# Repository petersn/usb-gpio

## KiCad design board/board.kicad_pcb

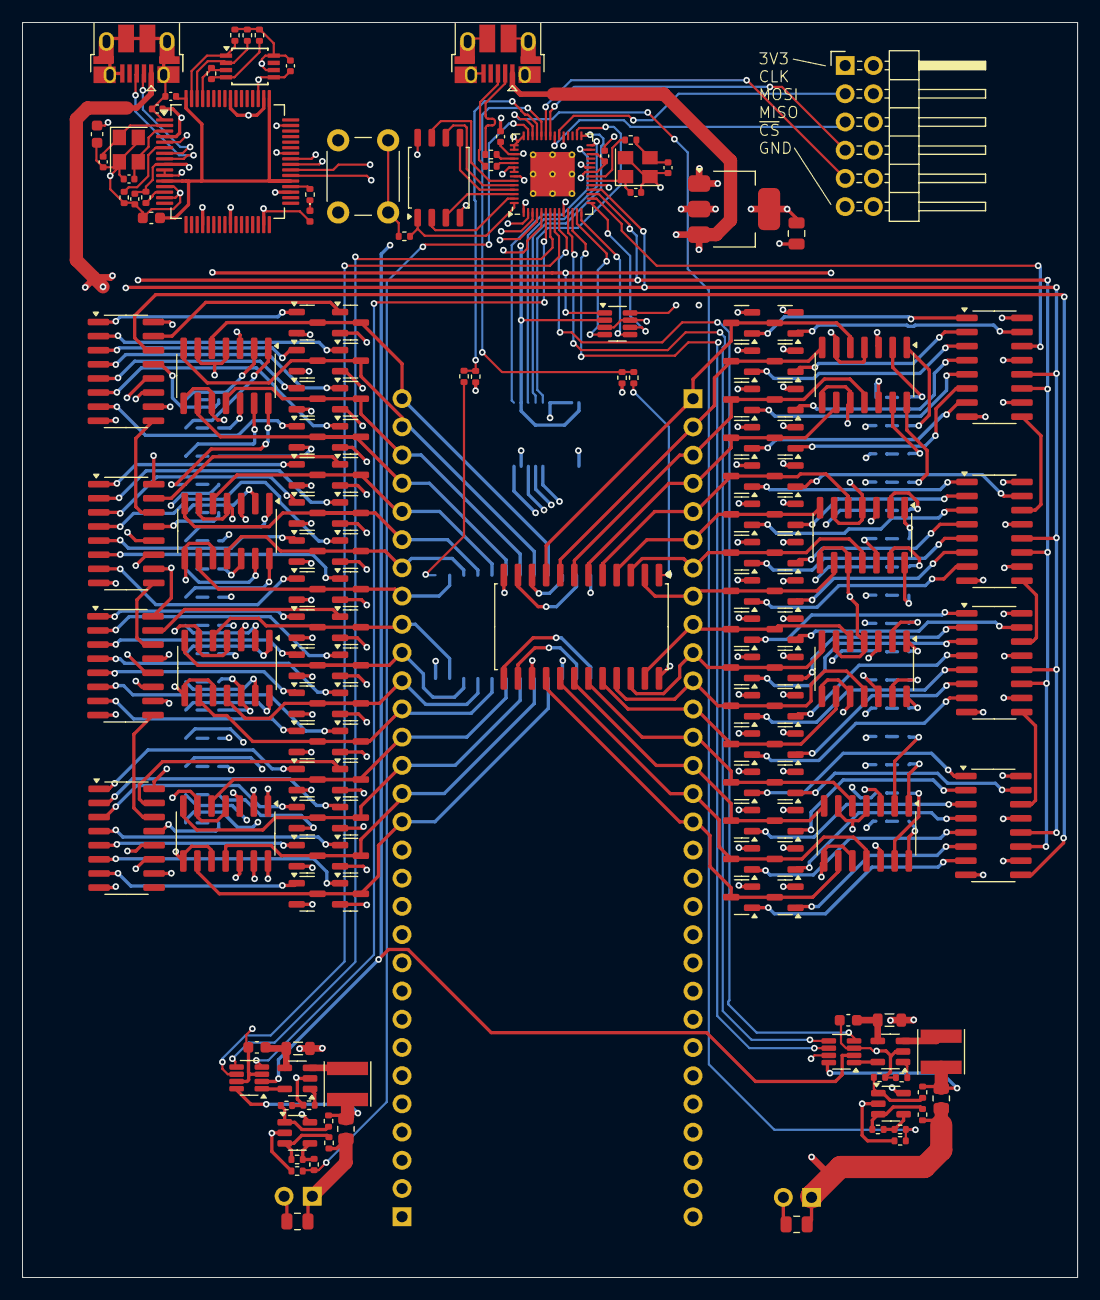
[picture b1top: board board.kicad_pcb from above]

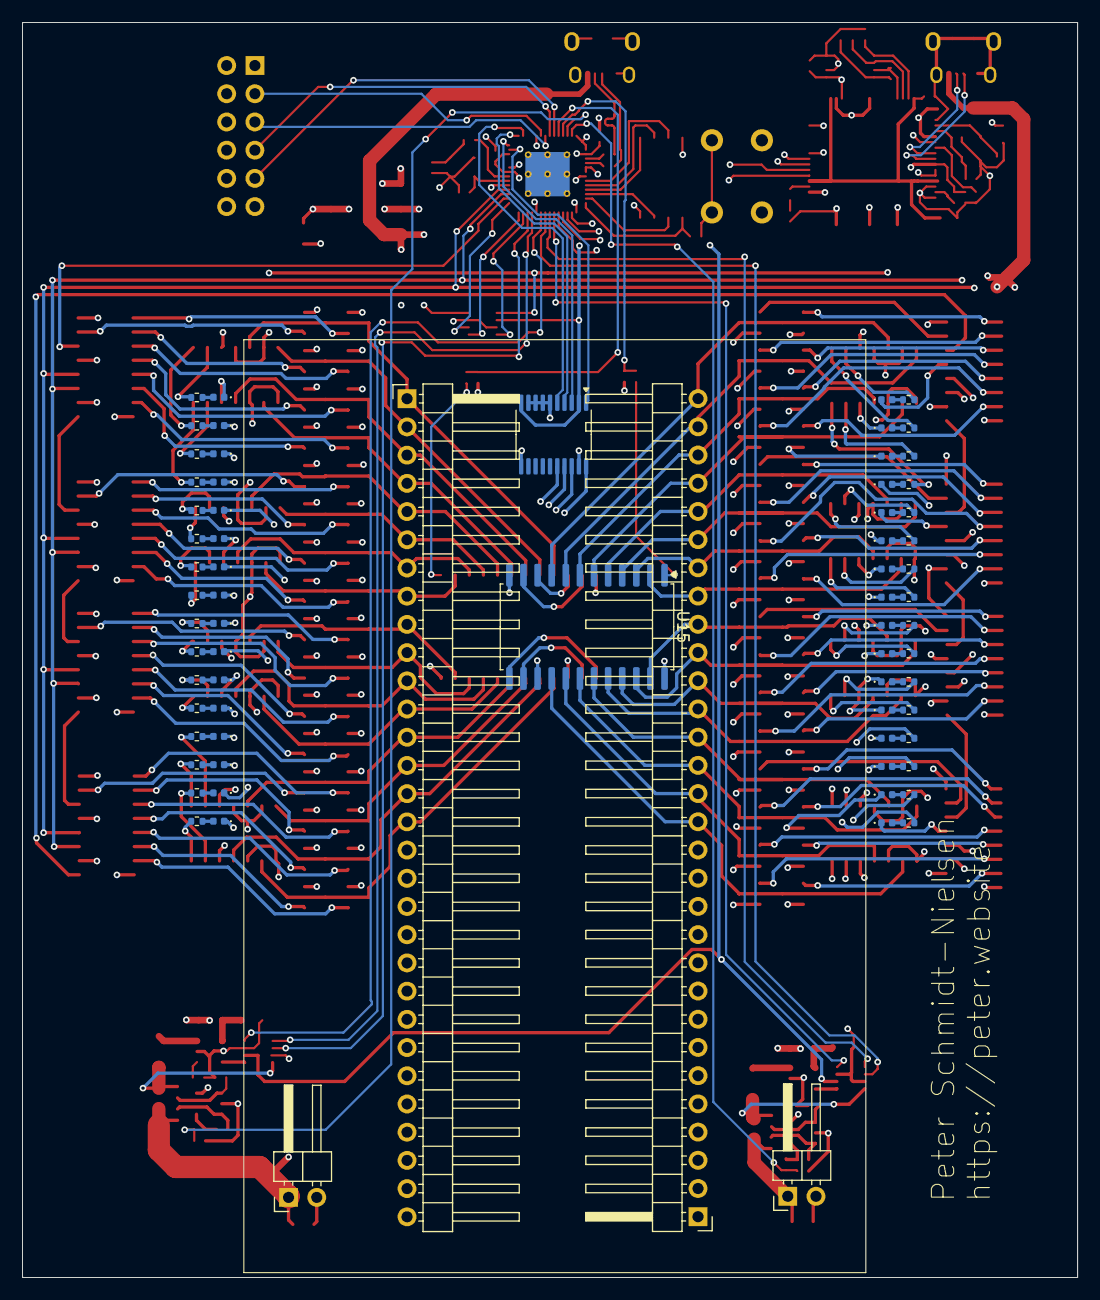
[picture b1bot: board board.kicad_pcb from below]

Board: 4 copper layers, 95.0 x 113.0 mm, 222 parts (70 on the bottom side), 251 nets.

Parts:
C1, C2, C10, C11: 15p; C_0402_1005Metric
C3, C6, C7, C8: 100n; C_0402_1005Metric
C4, C5, C12, C13: 4.7u; C_0603_1608Metric
C9, C14, C15: 10u; C_0805_2012Metric
C16, C17: 1u; C_0402_1005Metric
D1, D2, D3, D4, D5, D6, D7, D8, D9, D10, D11, D12, D13, D14, D15, D16, D17, D18, D19, D20, D21, D22, D23, D24, D25, D26, D27, D28, D29, D30, D31, D32, D33: LED; LED_0402_1005Metric
FB1, FB2: Ferrite_Bead_Small; L_0805_2012Metric
J1, J2: USB_B_Micro; USB_Micro-B_Amphenol_10103594-0001LF_Horizontal
J3, J5: Conn_01x30; PinHeader_1x30_P2.54mm_Horizontal
J4: Conn_02x06_Odd_Even; PinHeader_2x06_P2.54mm_Horizontal
J7, J8: Conn_01x02; PinHeader_1x02_P2.54mm_Horizontal
L1, L2: 2.2uH; L_Taiyo-Yuden_NR-40xx
Q1, Q3, Q5, Q7, Q9, Q11, Q13, Q15, Q17, Q19, Q21, Q23, Q25, Q27, Q29, Q31, Q33, Q35, Q37, Q39, Q41, Q43, Q45, Q47, Q49, Q51, Q53, Q55, Q57, Q59, Q61, Q63: Q_PMOS_GSD; SOT-23
Q2, Q4, Q6, Q8, Q10, Q12, Q14, Q16, Q18, Q20, Q22, Q24, Q26, Q28, Q30, Q32, Q34, Q36, Q38, Q40, Q42, Q44, Q46, Q48, Q50, Q52, Q54, Q56, Q58, Q60, Q62, Q64: Q_NMOS_GSD; SOT-23
R1: 12k; R_0402_1005Metric
R2, R3, R6, R20, R22, R62, R63: 10k; R_0402_1005Metric
R4: 2.2k; R_0402_1005Metric
R5, R8, R9, R12, R13, R16, R17, R30, R31, R32, R33, R34, R35, R36, R37, R38, R39, R40, R41, R42, R43, R44, R45, R46, R47, R48, R49, R50, R51, R52, R53, R54, R55, R56, R57, R58, R59, R60, R61: 1k; R_0402_1005Metric
R7: 220; R_0402_1005Metric
R10, R11, R18, R19: 49.9k; R_0402_1005Metric
R14, R15: 100m; R_0805_2012Metric
R21, R23: 15k; R_0402_1005Metric
R24, R25: 27; R_0402_1005Metric
R26, R28: 100k; R_0402_1005Metric
R27, R29: 150k; R_0402_1005Metric
SW1: SW_Omron_B3FS; SW_PUSH_6mm
U1: 93CxxC; TSSOP-8_3x3mm_P0.65mm
U2: FT2232HL; LQFP-64_10x10mm_P0.5mm
U3: NCP1117-3.3_SOT223; SOT-223-3_TabPin2
U4: W25Q128JVS; SOIC-8_5.23x5.23mm_P1.27mm
U5, U7: TLV62568DBV; SOT-23-5
U6, U8, U9: TPL0501-100DCNR; SOT-23-8
U10, U11: LM321; SOT-23-5
U12: RP2040; QFN-56-1EP_7x7mm_P0.4mm_EP4x4mm_ThermalVias
U13: TXS0108EPW; TSSOP-20_4.4x6.5mm_P0.65mm
U14, U15: CD74HC4067M; SOIC-24W_7.5x15.4mm_P1.27mm
U16, U18, U20, U22, U24, U26, U28, U30: 74HC595; SOIC-16_3.9x9.9mm_P1.27mm
U17, U19, U21, U23, U25, U27, U29, U31: LM2901; SOIC-14_3.9x8.7mm_P1.27mm
Y1, Y2: ABM8-272-T3; Crystal_SMD_3225-4Pin_3.2x2.5mm

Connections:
+1V1: C16.1, U12.23 (DVDD), U12.45 (VREG_VOUT), U12.50 (DVDD)
+3V3: C3.1, C5.1, C7.1, C8.1, C9.1, C17.1, D1.2 (A), J4.1, R2.2, R3.2, R5.1, R6.2, U1.6 (ORG), U1.8 (VCC), U2.4 (VPHY), U2.9 (VPLL), U2.20 (VCCIO), U2.31 (VCCIO), U2.42 (VCCIO), U2.50 (VREGIN), U2.56 (VCCIO), U3.2 (VO), U4.8 (VCC), U6.2 (VDD), U8.2 (VDD), U9.2 (VDD), U12.1 (IOVDD), U12.10 (IOVDD), U12.22 (IOVDD), U12.26 (RUN), U12.33 (IOVDD), U12.42 (IOVDD), U12.43 (ADC_AVDD), U12.44 (VREG_IN), U12.48 (USB_VDD), U12.49 (IOVDD), U13.2 (VCCA), U13.10 (OE)
/CTRL_CS: U2.41 (BDBUS3), U12.3 (GPIO1)
/CTRL_MISO: U2.40 (BDBUS2), U12.5 (GPIO3)
/CTRL_MOSI: U2.39 (BDBUS1), U12.2 (GPIO0)
/CTRL_SCK: U2.38 (BDBUS0), U12.4 (GPIO2)
/CURRENT_SENSE_A: R20.2, R21.1, U12.40 (GPIO28_ADC2)
/CURRENT_SENSE_B: R22.2, R23.1, U12.41 (GPIO29_ADC3)
/FTDI_1V8: C4.1, C6.1, U2.12 (VCORE), U2.37 (VCORE), U2.49 (VREGOUT), U2.64 (VCORE)
/LCD_CS: J4.9, U12.37 (GPIO25)
/LCD_MISO: J4.7, U12.36 (GPIO24)
/LCD_MOSI: J4.5, U12.35 (GPIO23)
/LCD_SCK: J4.3, U12.34 (GPIO22)
/LOGIC_THRESH: U9.1 (W), U17.4 (-), U17.6 (-), U17.8 (-), U17.10 (-), U19.4 (-), U19.6 (-), U19.8 (-), U19.10 (-), U21.4 (-), U21.6 (-), U21.8 (-), U21.10 (-), U23.4 (-), U23.6 (-), U23.8 (-), U23.10 (-), U25.4 (-), U25.6 (-), U25.8 (-), U25.10 (-), U27.4 (-), U27.6 (-), U27.8 (-), U27.10 (-), U29.4 (-), U29.6 (-), U29.8 (-), U29.10 (-), U31.4 (-), U31.6 (-), U31.8 (-), U31.10 (-)
/MUX_ADDR0: U12.27 (GPIO16), U13.1 (A1)
/MUX_ADDR0_5V: U13.20 (B1), U14.10 (S0), U15.10 (S0)
/MUX_ADDR1: U12.28 (GPIO17), U13.3 (A2)
/MUX_ADDR1_5V: U13.18 (B2), U14.11 (S1), U15.11 (S1)
/MUX_ADDR2: U12.29 (GPIO18), U13.4 (A3)
/MUX_ADDR2_5V: U13.17 (B3), U14.14 (S2), U15.14 (S2)
/MUX_ADDR3: U12.30 (GPIO19), U13.5 (A4)
/MUX_ADDR3_5V: U13.16 (B4), U14.13 (S3), U15.13 (S3)
/PIN0: J3.1, Q1.3 (D), Q2.3 (D), U14.9 (I0), U17.5 (+)
/PIN1: J3.2, Q3.3 (D), Q4.3 (D), U14.8 (I1), U17.7 (+)
/PIN2: J3.3, Q5.3 (D), Q6.3 (D), U14.7 (I2), U17.11 (+)
/PIN3: J3.4, Q7.3 (D), Q8.3 (D), U14.6 (I3), U17.9 (+)
/PIN4: J3.5, Q9.3 (D), Q10.3 (D), U14.5 (I4), U19.5 (+)
/PIN5: J3.6, Q11.3 (D), Q12.3 (D), U14.4 (I5), U19.7 (+)
/PIN6: J3.7, Q13.3 (D), Q14.3 (D), U14.3 (I6), U19.11 (+)
/PIN7: J3.8, Q15.3 (D), Q16.3 (D), U14.2 (I7), U19.9 (+)
/PIN8: J3.9, Q17.3 (D), Q18.3 (D), U14.23 (I8), U21.5 (+)
/PIN9: J3.10, Q19.3 (D), Q20.3 (D), U14.22 (I9), U21.7 (+)
/PIN10: J3.11, Q21.3 (D), Q22.3 (D), U14.21 (I10), U21.11 (+)
/PIN11: J3.12, Q23.3 (D), Q24.3 (D), U14.20 (I11), U21.9 (+)
/PIN12: J3.13, Q25.3 (D), Q26.3 (D), U14.19 (I12), U23.5 (+)
/PIN13: J3.14, Q27.3 (D), Q28.3 (D), U14.18 (I13), U23.7 (+)
/PIN14: J3.15, Q29.3 (D), Q30.3 (D), U14.17 (I14), U23.11 (+)
/PIN15: J3.16, Q31.3 (D), Q32.3 (D), U14.16 (I15), U23.9 (+)
/PIN16: J5.30, Q33.3 (D), Q34.3 (D), U15.9 (I0), U25.5 (+)
/PIN17: J5.29, Q35.3 (D), Q36.3 (D), U15.8 (I1), U25.7 (+)
/PIN18: J5.28, Q37.3 (D), Q38.3 (D), U15.7 (I2), U25.11 (+)
/PIN19: J5.27, Q39.3 (D), Q40.3 (D), U15.6 (I3), U25.9 (+)
/PIN20: J5.26, Q41.3 (D), Q42.3 (D), U15.5 (I4), U27.5 (+)
/PIN21: J5.25, Q43.3 (D), Q44.3 (D), U15.4 (I5), U27.7 (+)
/PIN22: J5.24, Q45.3 (D), Q46.3 (D), U15.3 (I6), U27.11 (+)
/PIN23: J5.23, Q47.3 (D), Q48.3 (D), U15.2 (I7), U27.9 (+)
/PIN24: J5.22, Q49.3 (D), Q50.3 (D), U15.23 (I8), U29.5 (+)
/PIN25: J5.21, Q51.3 (D), Q52.3 (D), U15.22 (I9), U29.7 (+)
/PIN26: J5.20, Q53.3 (D), Q54.3 (D), U15.21 (I10), U29.11 (+)
/PIN27: J5.19, Q55.3 (D), Q56.3 (D), U15.20 (I11), U29.9 (+)
/PIN28: J5.18, Q57.3 (D), Q58.3 (D), U15.19 (I12), U31.5 (+)
/PIN29: J5.17, Q59.3 (D), Q60.3 (D), U15.18 (I13), U31.7 (+)
/PIN30: J5.16, Q61.3 (D), Q62.3 (D), U15.17 (I14), U31.11 (+)
/PIN31: J5.15, Q63.3 (D), Q64.3 (D), U15.16 (I15), U31.9 (+)
/PIN_SENSE0: R26.2, R27.1, U12.38 (GPIO26_ADC0)
/PIN_SENSE1: R28.2, R29.1, U12.39 (GPIO27_ADC1)
/PROG_USB_D+: J2.3 (D+), R24.1
/PROG_USB_D-: J2.2 (D-), R25.1
/PWR_A: C14.1, J7.1, Q1.2 (S), Q3.2 (S), Q5.2 (S), Q7.2 (S), Q9.2 (S), Q11.2 (S), Q13.2 (S), Q15.2 (S), Q17.2 (S), Q19.2 (S), Q21.2 (S), Q23.2 (S), Q25.2 (S), Q27.2 (S), Q29.2 (S), Q31.2 (S), Q33.2 (S), Q35.2 (S), Q37.2 (S), Q39.2 (S), Q41.2 (S), Q43.2 (S), Q45.2 (S), Q47.2 (S), Q49.2 (S), Q51.2 (S), Q53.2 (S), Q55.2 (S), Q57.2 (S), Q59.2 (S), Q61.2 (S), Q63.2 (S), R14.2, R16.1
/PWR_A_DIN: U6.5 (DIN), U12.11 (GPIO8)
/PWR_A_EN: R62.2, U5.1 (EN)
/PWR_A_SCLK: U6.4 (SCLK), U12.9 (GPIO7)
/PWR_A_~CS: U6.6 (~CS), U12.12 (GPIO9)
/PWR_B: C15.1, J8.1, R15.2, R17.1
/PWR_B_DIN: U8.5 (DIN), U12.7 (GPIO5)
/PWR_B_EN: R63.2, U7.1 (EN)
/PWR_B_SCLK: U8.4 (SCLK), U12.6 (GPIO4)
/PWR_B_~CS: U8.6 (~CS), U12.8 (GPIO6)
/PinGroup0/DRIVE_HI_PIN0: Q1.1 (G), U16.15 (QA)
/PinGroup0/DRIVE_HI_PIN1: Q3.1 (G), U16.2 (QC)
/PinGroup0/DRIVE_HI_PIN2: Q5.1 (G), U16.4 (QE)
/PinGroup0/DRIVE_HI_PIN3: Q7.1 (G), U16.6 (QG)
/PinGroup0/DRIVE_LO_PIN0: Q2.1 (G), U16.1 (QB)
/PinGroup0/DRIVE_LO_PIN1: Q4.1 (G), U16.3 (QD)
/PinGroup0/DRIVE_LO_PIN2: Q6.1 (G), U16.5 (QF)
/PinGroup0/DRIVE_LO_PIN3: Q8.1 (G), U16.7 (QH)
/PinGroup0/SHIFT_OUT: U16.9 (QH'), U18.14 (SER)
/PinGroup1/DRIVE_HI_PIN0: Q9.1 (G), U18.15 (QA)
/PinGroup1/DRIVE_HI_PIN1: Q11.1 (G), U18.2 (QC)
/PinGroup1/DRIVE_HI_PIN2: Q13.1 (G), U18.4 (QE)
/PinGroup1/DRIVE_HI_PIN3: Q15.1 (G), U18.6 (QG)
/PinGroup1/DRIVE_LO_PIN0: Q10.1 (G), U18.1 (QB)
/PinGroup1/DRIVE_LO_PIN1: Q12.1 (G), U18.3 (QD)
/PinGroup1/DRIVE_LO_PIN2: Q14.1 (G), U18.5 (QF)
/PinGroup1/DRIVE_LO_PIN3: Q16.1 (G), U18.7 (QH)
/PinGroup1/SHIFT_OUT: U18.9 (QH'), U20.14 (SER)
/PinGroup2/DRIVE_HI_PIN0: Q17.1 (G), U20.15 (QA)
/PinGroup2/DRIVE_HI_PIN1: Q19.1 (G), U20.2 (QC)
/PinGroup2/DRIVE_HI_PIN2: Q21.1 (G), U20.4 (QE)
/PinGroup2/DRIVE_HI_PIN3: Q23.1 (G), U20.6 (QG)
/PinGroup2/DRIVE_LO_PIN0: Q18.1 (G), U20.1 (QB)
/PinGroup2/DRIVE_LO_PIN1: Q20.1 (G), U20.3 (QD)
/PinGroup2/DRIVE_LO_PIN2: Q22.1 (G), U20.5 (QF)
/PinGroup2/DRIVE_LO_PIN3: Q24.1 (G), U20.7 (QH)
/PinGroup2/SHIFT_OUT: U20.9 (QH'), U22.14 (SER)
/PinGroup3/DRIVE_HI_PIN0: Q25.1 (G), U22.15 (QA)
/PinGroup3/DRIVE_HI_PIN1: Q27.1 (G), U22.2 (QC)
/PinGroup3/DRIVE_HI_PIN2: Q29.1 (G), U22.4 (QE)
/PinGroup3/DRIVE_HI_PIN3: Q31.1 (G), U22.6 (QG)
/PinGroup3/DRIVE_LO_PIN0: Q26.1 (G), U22.1 (QB)
/PinGroup3/DRIVE_LO_PIN1: Q28.1 (G), U22.3 (QD)
/PinGroup3/DRIVE_LO_PIN2: Q30.1 (G), U22.5 (QF)
/PinGroup3/DRIVE_LO_PIN3: Q32.1 (G), U22.7 (QH)
/PinGroup3/SHIFT_OUT: U22.9 (QH'), U24.14 (SER)
/PinGroup4/DRIVE_HI_PIN0: Q33.1 (G), U24.15 (QA)
/PinGroup4/DRIVE_HI_PIN1: Q35.1 (G), U24.2 (QC)
/PinGroup4/DRIVE_HI_PIN2: Q37.1 (G), U24.4 (QE)
/PinGroup4/DRIVE_HI_PIN3: Q39.1 (G), U24.6 (QG)
/PinGroup4/DRIVE_LO_PIN0: Q34.1 (G), U24.1 (QB)
/PinGroup4/DRIVE_LO_PIN1: Q36.1 (G), U24.3 (QD)
/PinGroup4/DRIVE_LO_PIN2: Q38.1 (G), U24.5 (QF)
/PinGroup4/DRIVE_LO_PIN3: Q40.1 (G), U24.7 (QH)
/PinGroup4/SHIFT_OUT: U24.9 (QH'), U26.14 (SER)
/PinGroup5/DRIVE_HI_PIN0: Q41.1 (G), U26.15 (QA)
/PinGroup5/DRIVE_HI_PIN1: Q43.1 (G), U26.2 (QC)
/PinGroup5/DRIVE_HI_PIN2: Q45.1 (G), U26.4 (QE)
/PinGroup5/DRIVE_HI_PIN3: Q47.1 (G), U26.6 (QG)
/PinGroup5/DRIVE_LO_PIN0: Q42.1 (G), U26.1 (QB)
/PinGroup5/DRIVE_LO_PIN1: Q44.1 (G), U26.3 (QD)
/PinGroup5/DRIVE_LO_PIN2: Q46.1 (G), U26.5 (QF)
/PinGroup5/DRIVE_LO_PIN3: Q48.1 (G), U26.7 (QH)
/PinGroup5/SHIFT_OUT: U26.9 (QH'), U28.14 (SER)
/PinGroup6/DRIVE_HI_PIN0: Q49.1 (G), U28.15 (QA)
/PinGroup6/DRIVE_HI_PIN1: Q51.1 (G), U28.2 (QC)
/PinGroup6/DRIVE_HI_PIN2: Q53.1 (G), U28.4 (QE)
/PinGroup6/DRIVE_HI_PIN3: Q55.1 (G), U28.6 (QG)
/PinGroup6/DRIVE_LO_PIN0: Q50.1 (G), U28.1 (QB)
/PinGroup6/DRIVE_LO_PIN1: Q52.1 (G), U28.3 (QD)
/PinGroup6/DRIVE_LO_PIN2: Q54.1 (G), U28.5 (QF)
/PinGroup6/DRIVE_LO_PIN3: Q56.1 (G), U28.7 (QH)
/PinGroup6/SHIFT_OUT: U28.9 (QH'), U30.14 (SER)
/PinGroup7/DRIVE_HI_PIN0: Q57.1 (G), U30.15 (QA)
/PinGroup7/DRIVE_HI_PIN1: Q59.1 (G), U30.2 (QC)
/PinGroup7/DRIVE_HI_PIN2: Q61.1 (G), U30.4 (QE)
/PinGroup7/DRIVE_HI_PIN3: Q63.1 (G), U30.6 (QG)
/PinGroup7/DRIVE_LO_PIN0: Q58.1 (G), U30.1 (QB)
/PinGroup7/DRIVE_LO_PIN1: Q60.1 (G), U30.3 (QD)
/PinGroup7/DRIVE_LO_PIN2: Q62.1 (G), U30.5 (QF)
/PinGroup7/DRIVE_LO_PIN3: Q64.1 (G), U30.7 (QH)
/QSPI_SCLK: U4.6 (CLK), U12.52 (QSPI_SCLK)
/QSPI_SD0: U4.5 (DI(IO0)), U12.53 (QSPI_SD0)
/QSPI_SD1: U4.2 (DO(IO1)), U12.55 (QSPI_SD1)
/QSPI_SD2: U4.3 (IO2), U12.54 (QSPI_SD2)
/QSPI_SD3: U4.7 (IO3), U12.51 (QSPI_SD3)
/QSPI_SS: R8.1, U4.1 (~CS), U12.56 (QSPI_SS)
/REG_CLK: U12.18 (GPIO15), U16.12 (RCLK), U18.12 (RCLK), U20.12 (RCLK), U22.12 (RCLK), U24.12 (RCLK), U26.12 (RCLK), U28.12 (RCLK), U30.12 (RCLK)
/SHIFT_CLK: U12.17 (GPIO14), U16.11 (SRCLK), U18.11 (SRCLK), U20.11 (SRCLK), U22.11 (SRCLK), U24.11 (SRCLK), U26.11 (SRCLK), U28.11 (SRCLK), U30.11 (SRCLK)
/SHIFT_IN: U12.16 (GPIO13), U16.14 (SER)
/THRESH_DIN: U9.5 (DIN), U12.14 (GPIO11)
/THRESH_SCLK: U9.4 (SCLK), U12.13 (GPIO10)
/THRESH_~CS: U9.6 (~CS), U12.15 (GPIO12)
/XIN: C10.1, U12.20 (XIN), Y2.1
/XOUT: R9.1, U12.21 (XOUT)
/~USB_BOOT: R8.2, SW1.2
GND: C1.2, C2.2, C3.2, C4.2, C5.2, C6.2, C7.2, C8.2, C9.2, C10.2, C11.2, C12.2, C13.2, C14.2, C15.2, C16.2, C17.2, D2.1 (K), D3.1 (K), D4.1 (K), D5.1 (K), D6.1 (K), D7.1 (K), D8.1 (K), D9.1 (K), D10.1 (K), D11.1 (K), D12.1 (K), D13.1 (K), D14.1 (K), D15.1 (K), D16.1 (K), D17.1 (K), D18.1 (K), D19.1 (K), D20.1 (K), D21.1 (K), D22.1 (K), D23.1 (K), D24.1 (K), D25.1 (K), D26.1 (K), D27.1 (K), D28.1 (K), D29.1 (K), D30.1 (K), D31.1 (K), D32.1 (K), D33.1 (K), J1.5 (GND), J1.6 (Shield), J2.5 (GND), J2.6 (Shield), J4.11, J7.2, J8.2, Q2.2 (S), Q4.2 (S), Q6.2 (S), Q8.2 (S), Q10.2 (S), Q12.2 (S), Q14.2 (S), Q16.2 (S), Q18.2 (S), Q20.2 (S), Q22.2 (S), Q24.2 (S), Q26.2 (S), Q28.2 (S), Q30.2 (S), Q32.2 (S), Q34.2 (S), Q36.2 (S), Q38.2 (S), Q40.2 (S), Q42.2 (S), Q44.2 (S), Q46.2 (S), Q48.2 (S), Q50.2 (S), Q52.2 (S), Q54.2 (S), Q56.2 (S), Q58.2 (S), Q60.2 (S), Q62.2 (S), Q64.2 (S), R1.2, R10.2, R11.2, R21.2, R23.2, R27.2, R29.2, R62.1, R63.1, SW1.1, U1.5 (GND), U2.1 (GND), U2.5 (GND), U2.10 (AGND), U2.11 (GND), U2.13 (TEST), U2.15 (GND), U2.25 (GND), U2.35 (GND), U2.47 (GND), U2.51 (GND), U3.1 (GND), U4.4 (GND), U5.2 (GND), U6.3 (GND), U6.7 (L), U7.2 (GND), U8.3 (GND), U8.7 (L), U9.3 (GND), U9.7 (L), U10.2 (V-), U11.2 (V-), U12.19 (TESTEN), U12.57 (GND), U13.6 (A5), U13.7 (A6), U13.8 (A7), U13.9 (A8), U13.11 (GND), U14.12 (GND), U14.15 (~E), U15.12 (GND), U15.15 (~E), U16.8 (GND), U16.13 (~OE), U17.12 (V-), U18.8 (GND), U18.13 (~OE), U19.12 (V-), U20.8 (GND), U20.13 (~OE), U21.12 (V-), U22.8 (GND), U22.13 (~OE), U23.12 (V-), U24.8 (GND), U24.13 (~OE), U25.12 (V-), U26.8 (GND), U26.13 (~OE), U27.12 (V-), U28.8 (GND), U28.13 (~OE), U29.12 (V-), U30.8 (GND), U30.13 (~OE), U31.12 (V-), Y1.2, Y1.4, Y2.2, Y2.4
unnamed: C11.1, R9.2, Y2.3
unnamed: D1.1 (K), R7.1
unnamed: D2.2 (A), R30.2
unnamed: D3.2 (A), R31.2
unnamed: D4.2 (A), R32.2
unnamed: D5.2 (A), R33.2
unnamed: D6.2 (A), R34.2
unnamed: D7.2 (A), R35.2
unnamed: D8.2 (A), R36.2
unnamed: D9.2 (A), R37.2
unnamed: D10.2 (A), R38.2
unnamed: D11.2 (A), R39.2
unnamed: D12.2 (A), R40.2
unnamed: D13.2 (A), R41.2
unnamed: D14.2 (A), R42.2
unnamed: D15.2 (A), R43.2
unnamed: D16.2 (A), R44.2
unnamed: D17.2 (A), R45.2
unnamed: D18.2 (A), R46.2
unnamed: D19.2 (A), R47.2
unnamed: D20.2 (A), R48.2
unnamed: D21.2 (A), R49.2
unnamed: D22.2 (A), R50.2
unnamed: D23.2 (A), R51.2
unnamed: D24.2 (A), R52.2
unnamed: D25.2 (A), R53.2
unnamed: D26.2 (A), R54.2
unnamed: D27.2 (A), R55.2
unnamed: D28.2 (A), R56.2
unnamed: D29.2 (A), R57.2
unnamed: D30.2 (A), R58.2
unnamed: D31.2 (A), R59.2
unnamed: D32.2 (A), R60.2
unnamed: D33.2 (A), R61.2
unnamed: J1.3 (D+), U2.8 (DP)
unnamed: J1.2 (D-), U2.7 (DM)
unnamed: R18.1, R20.1, U10.4
unnamed: R19.1, R22.1, U11.4
unnamed: R30.1, U17.2
unnamed: R31.1, U17.1
unnamed: R32.1, U17.13
unnamed: R33.1, U17.14
unnamed: R34.1, U19.2
unnamed: R35.1, U19.1
unnamed: R36.1, U19.13
unnamed: R37.1, U19.14
unnamed: R38.1, U21.2
unnamed: R39.1, U21.1
unnamed: R40.1, U21.13
unnamed: R41.1, U21.14
unnamed: R42.1, U23.2
unnamed: R43.1, U23.1
unnamed: R44.1, U23.13
unnamed: R45.1, U23.14
unnamed: R46.1, U25.2
unnamed: R47.1, U25.1
unnamed: R48.1, U25.13
unnamed: R49.1, U25.14
unnamed: R50.1, U27.2
unnamed: R51.1, U27.1
unnamed: R52.1, U27.13
unnamed: R53.1, U27.14
unnamed: R54.1, U29.2
unnamed: R55.1, U29.1
unnamed: R56.1, U29.13
unnamed: R57.1, U29.14
unnamed: R58.1, U31.2
unnamed: R59.1, U31.1
unnamed: R60.1, U31.13
unnamed: R61.1, U31.14
unnamed: R3.1, U1.1 (CS), U2.63 (EECS)
unnamed: R4.2, U1.3 (DI), U2.61 (EEDATA)
unnamed: R2.1, R4.1, U1.4 (DO)
unnamed: R6.1, U1.2 (SCLK), U2.62 (EECLK)
unnamed: C1.1, U2.2 (OSCI), Y1.1
unnamed: C2.1, U2.3 (OSCO), Y1.3
unnamed: R1.1, U2.6 (REF)
unnamed: R5.2, U2.14 (~RESET)
unnamed: R7.2, U2.36 (~SUSPEND)
unnamed: U5.5 (FB), U6.1 (W)
unnamed: L1.1, U5.3 (SW)
unnamed: C12.1, FB1.1, U5.4 (VIN)
unnamed: L1.2, R12.1, R14.1, U6.8 (H)
unnamed: U7.5 (FB), U8.1 (W)
unnamed: L2.1, U7.3 (SW)
unnamed: C13.1, FB2.1, U7.4 (VIN)
unnamed: L2.2, R13.1, R15.1, U8.8 (H)
unnamed: R10.1, R12.2, U10.1 (+)
unnamed: R16.2, R18.2, U10.3 (-)
unnamed: R11.1, R13.2, U11.1 (+)
unnamed: R17.2, R19.2, U11.3 (-)
unnamed: R25.2, U12.46 (USB_DM)
unnamed: R24.2, U12.47 (USB_DP)
unnamed: R26.1, U14.1 (COM)
unnamed: R28.1, U15.1 (COM)
VBUS: FB1.2, FB2.2, J1.1 (VBUS), J2.1 (VBUS), U3.3 (VI), U9.8 (H), U10.5 (V+), U11.5 (V+), U13.19 (VCCB), U14.24 (VCC), U15.24 (VCC), U16.10 (~SRCLR), U16.16 (VCC), U17.3 (V+), U18.10 (~SRCLR), U18.16 (VCC), U19.3 (V+), U20.10 (~SRCLR), U20.16 (VCC), U21.3 (V+), U22.10 (~SRCLR), U22.16 (VCC), U23.3 (V+), U24.10 (~SRCLR), U24.16 (VCC), U25.3 (V+), U26.10 (~SRCLR), U26.16 (VCC), U27.3 (V+), U28.10 (~SRCLR), U28.16 (VCC), U29.3 (V+), U30.10 (~SRCLR), U30.16 (VCC), U31.3 (V+)

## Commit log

2024-05-16 Initial work
2024-05-17 More work before submitting
2024-05-17 First upload
